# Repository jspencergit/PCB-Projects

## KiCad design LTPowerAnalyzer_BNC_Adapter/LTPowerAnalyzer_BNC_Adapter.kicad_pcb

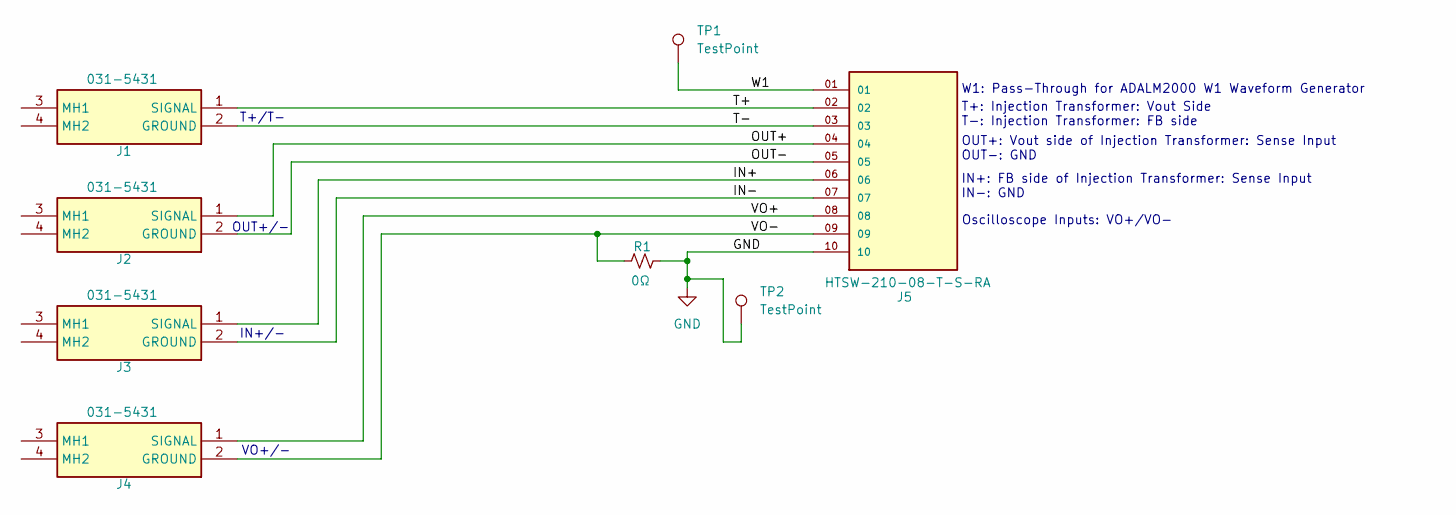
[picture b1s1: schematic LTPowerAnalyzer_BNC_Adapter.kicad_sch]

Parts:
J1, J2, J3, J4: 031-5431; 0315431; Mouser Part Number 523-31-5431
J5: HTSW-210-08-T-S-RA; SAMTEC_HTSW-210-08-T-S-RA; PARTREV R
R1: 0Ω; R_0805_2012Metric
TP1, TP2: TestPoint; TestPoint_Pad_1.5x1.5mm

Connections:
/IN+: J3.1 (SIGNAL), J5.06
/IN-: J3.2 (GROUND), J5.07
/OUT+: J2.1 (SIGNAL), J5.04
/OUT-: J2.2 (GROUND), J5.05
/T+: J1.1 (SIGNAL), J5.02
/T-: J1.2 (GROUND), J5.03
/VO+: J4.1 (SIGNAL), J5.08
/VO-: J4.2 (GROUND), J5.09, R1.1
/W1: J5.01, TP1.1
GND: J5.10, R1.2, TP2.1

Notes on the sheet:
T+/T-
T+: Injection Transformer: Vout Side T-: Injection Transformer: FB side
IN+: FB side of Injection Transformer: Sense Input IN-: GND
Oscilloscope Inputs: VO+/VO-
W1: Pass-Through for ADALM2000 W1 Waveform Generator
IN+/-
OUT+/-
VO+/-
OUT+: Vout side of Injection Transformer: Sense Input OUT-: GND

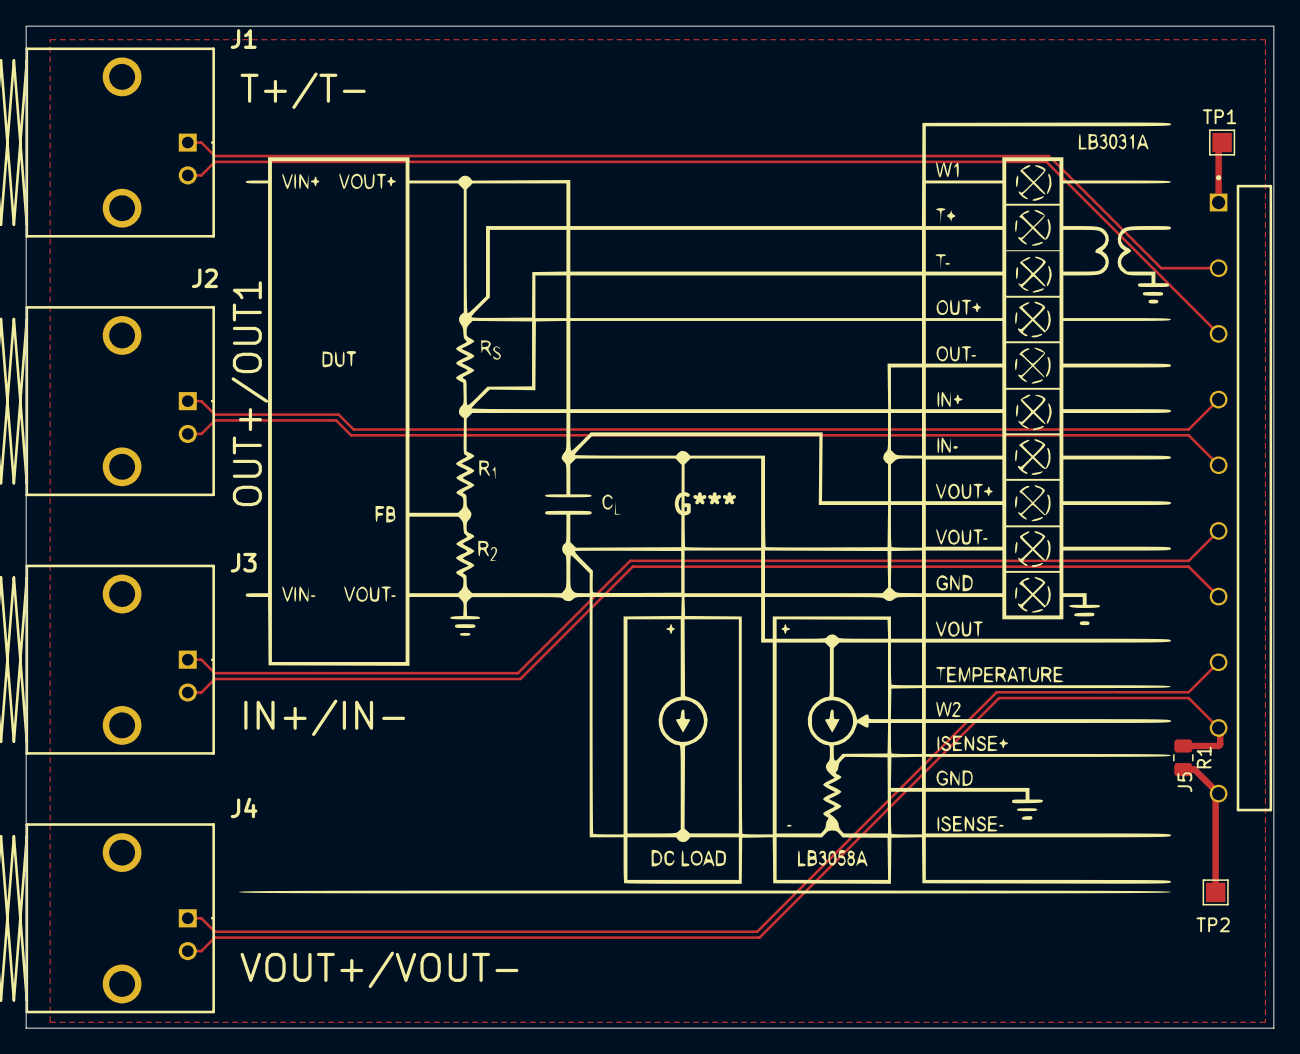
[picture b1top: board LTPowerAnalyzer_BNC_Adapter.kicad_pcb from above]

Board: 2 copper layers, 96.5 x 77.5 mm, 8 parts (0 on the bottom side), 10 nets.

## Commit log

2025-03-28 Major update
2025-03-28 ignore some files
2025-03-28 ignore update
2025-03-28 remove backup files
2025-03-28 remove backup file
2025-03-30 routing
